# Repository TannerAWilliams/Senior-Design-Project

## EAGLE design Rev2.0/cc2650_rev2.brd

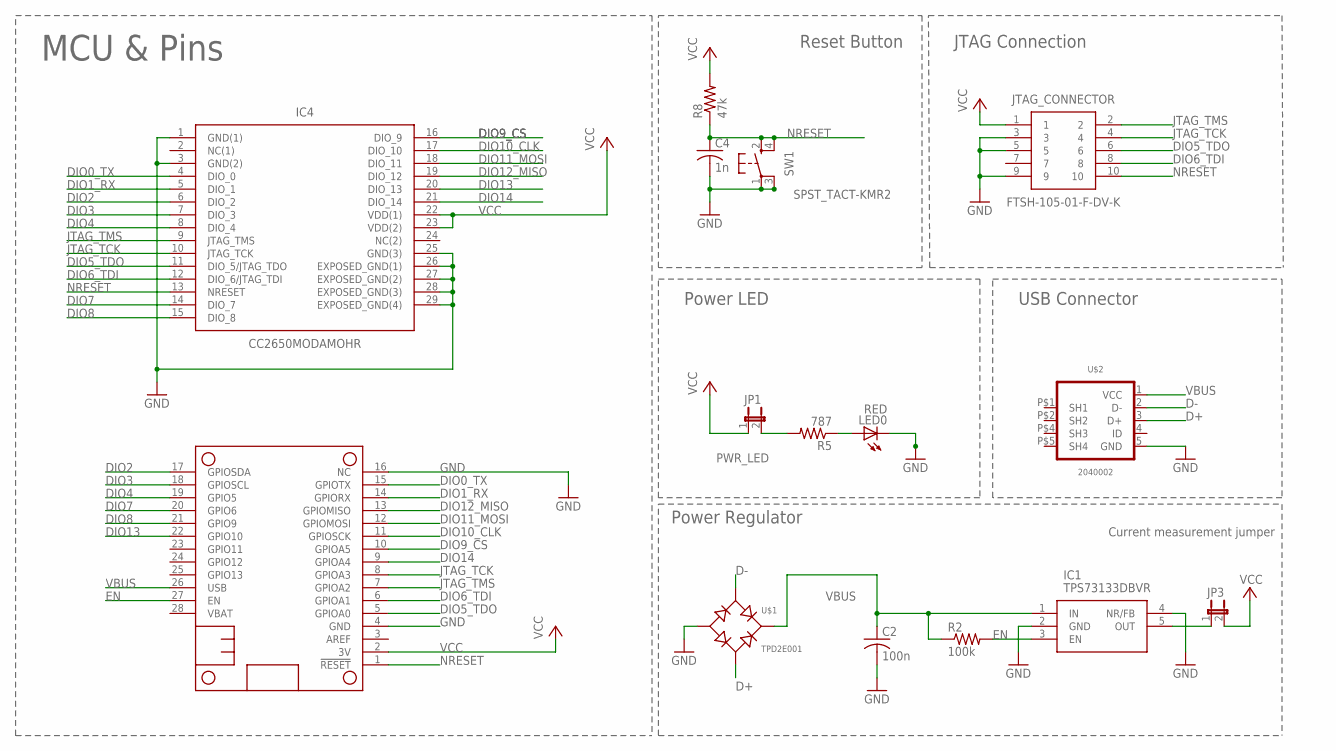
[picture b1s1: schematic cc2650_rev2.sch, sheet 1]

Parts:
C2: 100n; C1206
C4: 1n; C1206
IC1: TPS73133DBVR; SOT95P280X145-5N; MPN TPS73133DBVR
IC4: CC2650MODAMOHR; MOH0029A; MPN CC2650MODAMOHR
JP1, JP3: PWR_LED; JP1M; MPN 2211S-02G
JTAG_CONNECTOR: FTSH-105-01-F-DV-K; SAMTEC_FTSH-105-01-L-DV; MPN FTSH-105-01-F-DV-K
LED0: RED; CHIPLED_0603
MS1: FEATHERWING_NODIM; FEATHERWING_DIM
R2: 100k; R1206
R5: 787; R0603; MPN RC0603JR-07100KL
R8: 47k; R1206
SW1: SPST_TACT-KMR2; KMR2; MPN KMR241G LFS
U$1: TPD2E001; SOT-143
U$2: 2040002

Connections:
D+: U$1.3 (AC2), U$2.3 (D+)
D-: U$1.2 (AC1), U$2.2 (D-)
DIO0_TX: IC4.4 (DIO_0), MS1.15 (GPIOTX)
DIO1_RX: IC4.5 (DIO_1), MS1.14 (GPIORX)
DIO2: IC4.6 (DIO_2), MS1.17 (GPIOSDA); also elsewhere on the board
DIO3: IC4.7 (DIO_3), MS1.18 (GPIOSCL); also elsewhere on the board
DIO4: IC4.8 (DIO_4), MS1.19 (GPIO5)
DIO5_TDO: IC4.11 (DIO_5/JTAG_TDO), JTAG_CONNECTOR.6, MS1.5 (GPIOA0)
DIO6_TDI: IC4.12 (DIO_6/JTAG_TDI), JTAG_CONNECTOR.8, MS1.6 (GPIOA1)
DIO7: IC4.14 (DIO_7), MS1.20 (GPIO6)
DIO8: IC4.15 (DIO_8), MS1.21 (GPIO9)
DIO9_CS: IC4.16 (DIO_9), MS1.10 (GPIOA5)
DIO10_CLK: IC4.17 (DIO_10), MS1.11 (GPIOSCK)
DIO11_MOSI: IC4.18 (DIO_11), MS1.12 (GPIOMOSI)
DIO12_MISO: IC4.19 (DIO_12), MS1.13 (GPIOMISO)
DIO13: IC4.20 (DIO_13), MS1.22 (GPIO10); also elsewhere on the board
DIO14: IC4.21 (DIO_14), MS1.9 (GPIOA4); also elsewhere on the board
EN: IC1.3 (EN), MS1.27 (EN), R2.2
GND: C2.2, C4.2, IC1.2 (GND), IC1.4 (NR/FB), IC4.1 (GND(1)), IC4.3 (GND(2)), IC4.25 (GND(3)), IC4.26 (EXPOSED_GND(1)), IC4.27 (EXPOSED_GND(2)), IC4.28 (EXPOSED_GND(3)), IC4.29 (EXPOSED_GND(4)), JTAG_CONNECTOR.3, JTAG_CONNECTOR.5, JTAG_CONNECTOR.9, LED0.C, MS1.4 (GND), MS1.16 (NC), SW1.1, SW1.3 (P1), U$1.1 (-), U$2.5 (GND); also elsewhere on the board
JTAG_TCK: IC4.10 (JTAG_TCK), JTAG_CONNECTOR.4, MS1.8 (GPIOA3)
JTAG_TMS: IC4.9 (JTAG_TMS), JTAG_CONNECTOR.2, MS1.7 (GPIOA2)
NRESET: C4.1, IC4.13 (NRESET), JTAG_CONNECTOR.10, MS1.1 (!RESET), R8.1, SW1.2 (S), SW1.4 (S1)
PWR_LED: LED0.A, R5.1
PWR_LED_JPR: JP1.2, R5.2
VBUS: C2.1, IC1.1 (IN), MS1.26 (USB), R2.1, U$1.4 (+), U$2.1 (VCC)
VCC: IC4.22 (VDD(1)), IC4.23 (VDD(2)), JP1.1, JP3.2, JTAG_CONNECTOR.1, MS1.2 (3V), R8.2; also elsewhere on the board
VCC_JPR: IC1.5 (OUT), JP3.1

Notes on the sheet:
Current measurement jumper
JTAG Connection
Reset Button
Power Regulator
Power LED
USB Connector
MCU & Pins

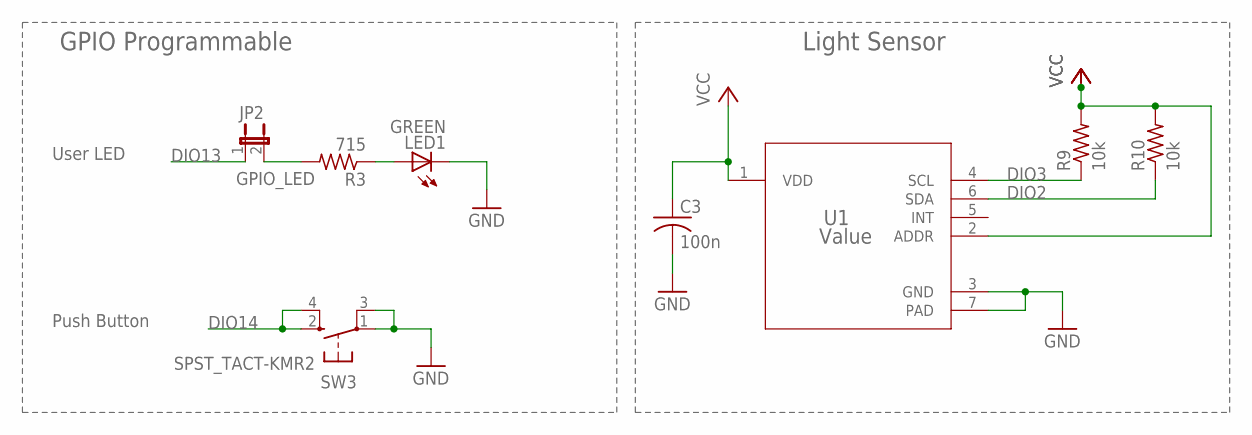
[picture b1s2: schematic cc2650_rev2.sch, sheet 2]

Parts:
C3: 100n; C1206
JP2: GPIO_LED; JP1M; MPN 2211S-02G
LED1: GREEN; CHIPLED_0603
R3: 715; R0603; MPN RC0603JR-07100KL
R9, R10: 10k; R1206
SW3: SPST_TACT-KMR2; KMR2; MPN KMR241G LFS
U1: Value; DNP0006A

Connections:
DIO2: R10.1, U1.6 (SDA); also elsewhere on the board
DIO3: R9.1, U1.4 (SCL); also elsewhere on the board
DIO13: JP2.1; also elsewhere on the board
DIO14: SW3.2 (S), SW3.4 (S1); also elsewhere on the board
GND: C3.2, LED1.C, SW3.1, SW3.3 (P1), U1.3 (GND), U1.7 (PAD); also elsewhere on the board
GPIO_LED: LED1.A, R3.1
GPIO_LED_JPR: JP2.2, R3.2
VCC: C3.1, R9.2, R10.2, U1.1 (VDD), U1.2 (ADDR); also elsewhere on the board

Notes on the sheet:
GPIO Programmable
User LED
Light Sensor
Push Button

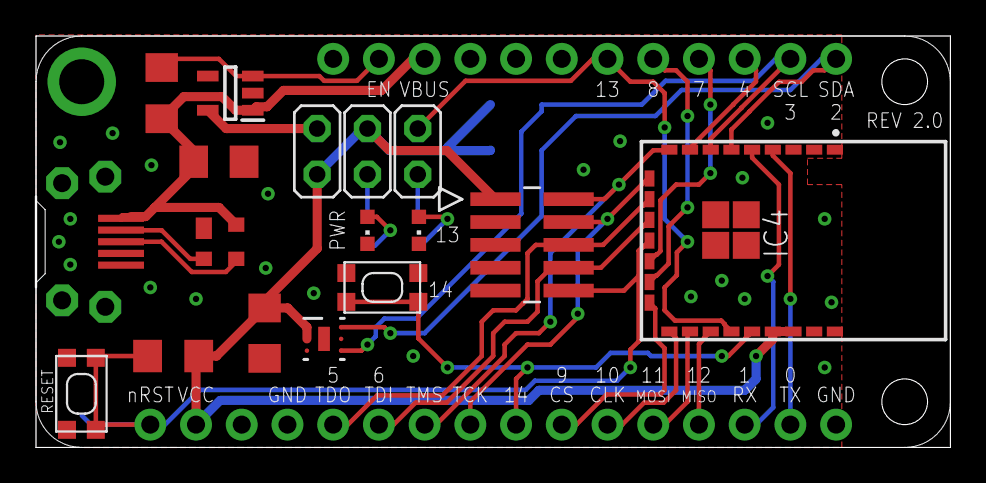
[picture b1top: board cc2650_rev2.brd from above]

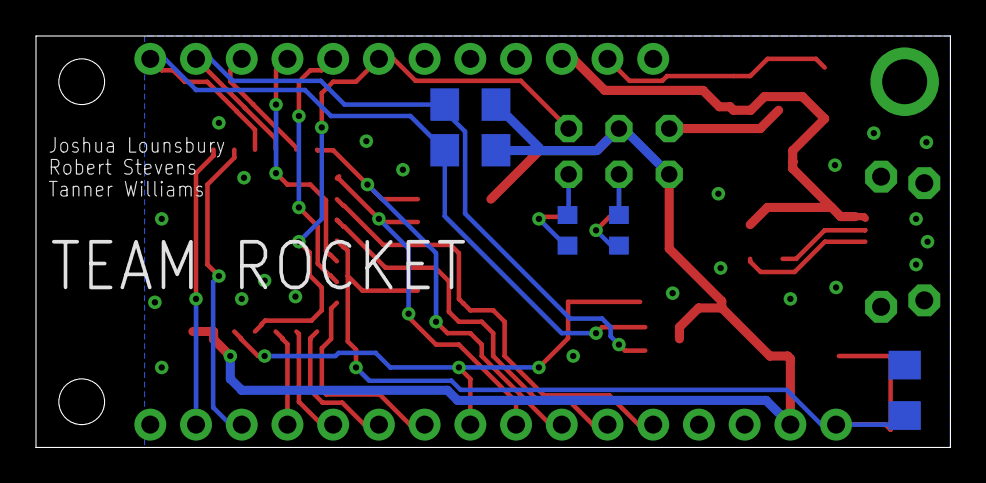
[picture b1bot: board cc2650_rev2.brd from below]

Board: 2 copper layers, 50.8 x 22.9 mm, 23 parts (5 on the bottom side), 29 nets.

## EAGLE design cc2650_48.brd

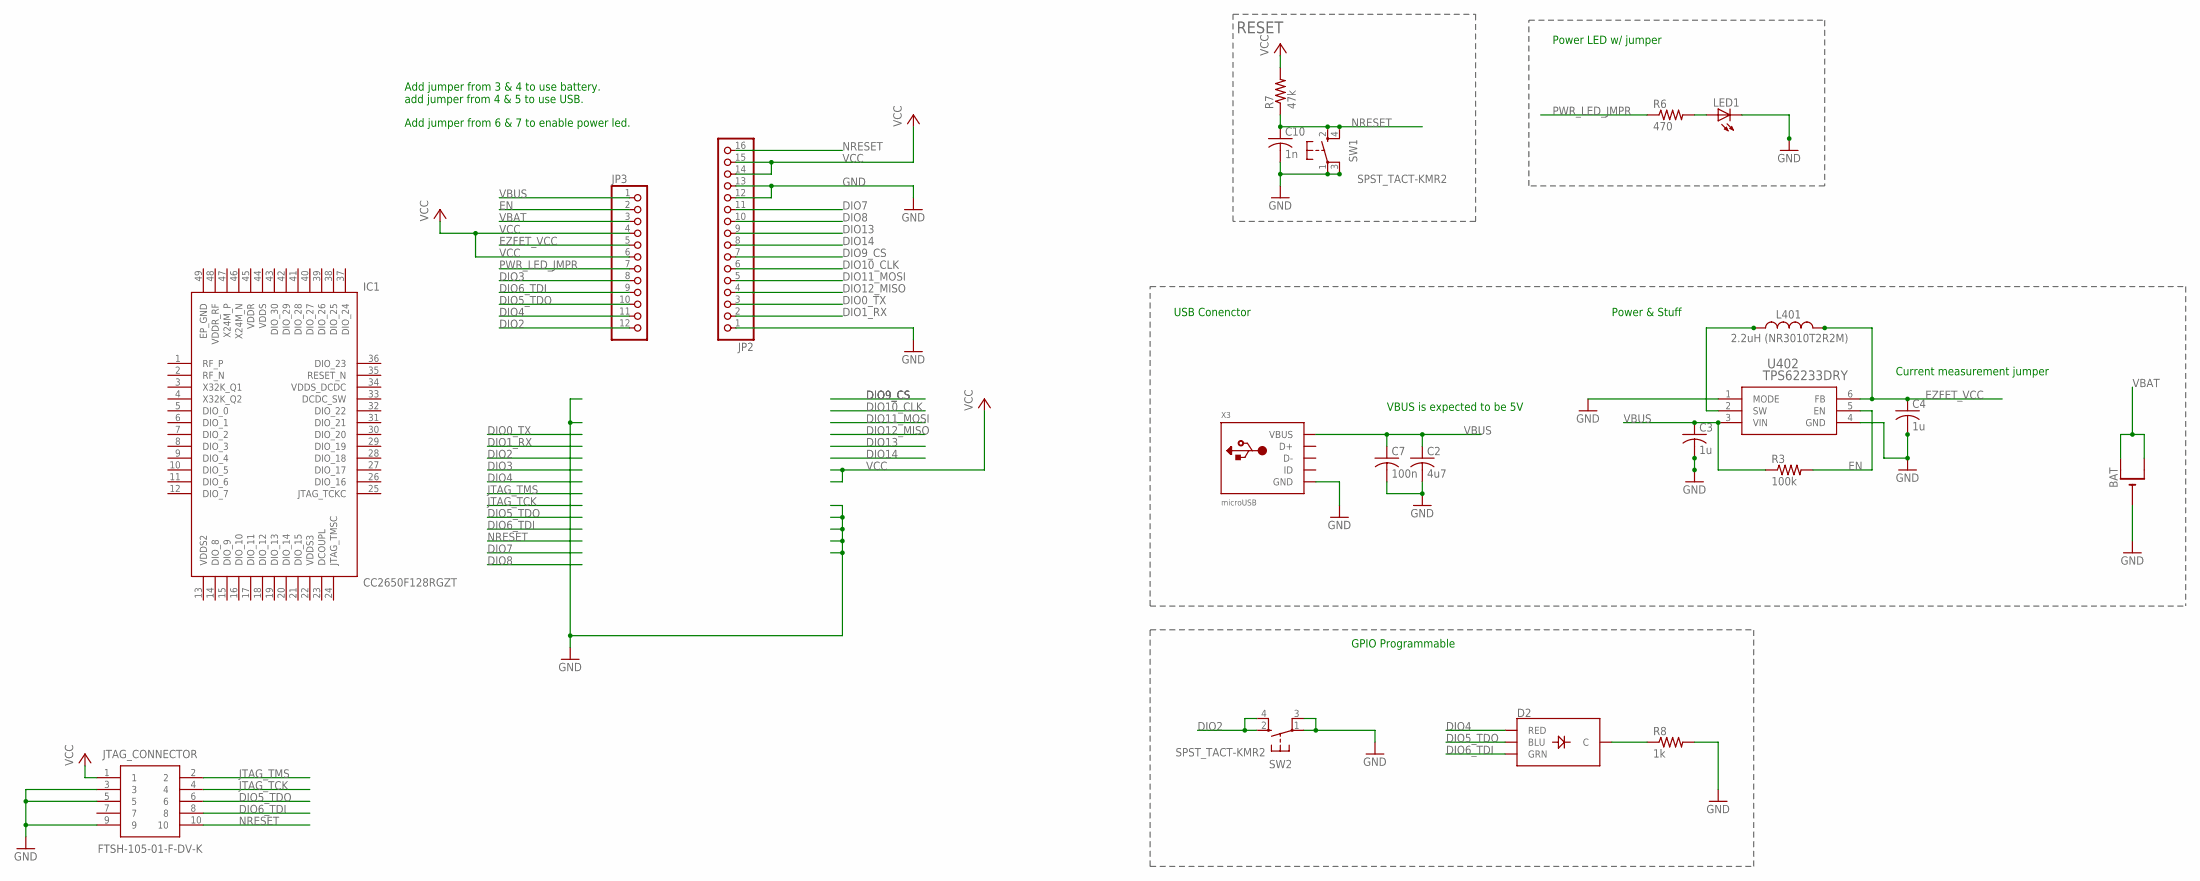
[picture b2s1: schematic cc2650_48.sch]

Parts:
BAT: CR1220THM; CR1220-THM; MPN 3000
C2: 4u7; C1206; MPN GRT31CC81E475KE01L
C3, C4: 1u; C0805; MPN C0805C105K5RACTU
C7: 100n; C0805
C10: 1n; C0805
D2: LED-RGB-CCPIRANHA; LED_PIRANHA_5MM; MPN CLMVB-FKA-CFHEHLCBB7A363
IC1: CC2650F128RGZT; QFN50P700X700X100-49N
JP2: HEADER-1X16ROUND; 1X16_ROUND
JP3: HEADER-1X12; 1X12_ROUND
JTAG_CONNECTOR: FTSH-105-01-F-DV-K; SAMTEC_FTSH-105-01-L-DV; MPN FTSH-105-01-F-DV-K
L401: 2.2uH (NR3010T2R2M); L-NR3010; MPN NR3010T2R2M
LED1: LEDCHIPLED_0805; CHIPLED_0805
R3: 100k; R0805
R6: 470; R0805
R7: 47k; R0805
R8: 1k; R0805
SW1, SW2: SPST_TACT-KMR2; KMR2
U402: TPS62233DRY; DRY6; MPN TPS62233DRYT
X3: microUSB; 4UCONN_20329_V2

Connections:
DIO0_TX: JP2.3
DIO1_RX: JP2.2
DIO2: JP3.12, SW2.2 (S), SW2.4 (S1)
DIO3: JP3.8
DIO4: D2.R (RED), JP3.11
DIO5_TDO: D2.B (BLU), JP3.10, JTAG_CONNECTOR.6
DIO6_TDI: D2.G (GRN), JP3.9, JTAG_CONNECTOR.8
DIO7: JP2.11
DIO8: JP2.10
DIO9_CS: JP2.7
DIO10_CLK: JP2.6
DIO11_MOSI: JP2.5
DIO12_MISO: JP2.4
DIO13: JP2.9
DIO14: JP2.8
EN: JP3.2, R3.2, U402.5 (EN)
EP_GND: IC1.49 (EP_GND)
EZFET_VCC: C4.1, JP3.5, L401.P$2 (2), U402.6 (FB)
GND: BAT.-, C2.2, C3.2, C4.2, C7.2, C10.2, JP2.1, JP2.12, JP2.13, JTAG_CONNECTOR.3, JTAG_CONNECTOR.5, JTAG_CONNECTOR.9, LED1.C, R8.2, SW1.1, SW1.3 (P1), SW2.1, SW2.3 (P1), U402.1 (MODE), U402.4 (GND), X3.BASE@1 (GND), X3.BASE@2 (GND), X3.GND, X3.SPRT@1 (GND), X3.SPRT@2 (GND), X3.SPRT@3 (GND), X3.SPRT@4 (GND)
JTAG_TCK: JTAG_CONNECTOR.4
JTAG_TMS: JTAG_CONNECTOR.2
unnamed: D2.- (C), R8.1
unnamed: L401.P$1 (1), U402.2 (SW)
unnamed: LED1.A, R6.2
NRESET: C10.1, JP2.16, JTAG_CONNECTOR.10, R7.1, SW1.2 (S), SW1.4 (S1)
PWR_LED_JMPR: JP3.7, R6.1
VBAT: BAT.+1 (+), BAT.+2 (+1), JP3.3
VBUS: C2.1, C3.1, C7.1, JP3.1, R3.1, U402.3 (VIN), X3.VBUS
VCC: JP2.14, JP2.15, JP3.4, JP3.6, JTAG_CONNECTOR.1, R7.2
VDDR: IC1.45 (VDDR)
VDDR_RF: IC1.48 (VDDR_RF)
VDDS: IC1.44 (VDDS)
VDDS2: IC1.13 (VDDS2)
VDDS3: IC1.22 (VDDS3)
VDDS_DCDC: IC1.34 (VDDS_DCDC)

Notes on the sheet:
USB Conenctor
RESET
Power LED w/ jumper
Power & Stuff
VBUS is expected to be 5V
Current measurement jumper
GPIO Programmable
Add jumper from 3 & 4 to use battery. add jumper from 4 & 5 to use USB.
Add jumper from 6 & 7 to enable power led.

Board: 2 copper layers, 21 parts (2 on the bottom side), 15 nets, no tracks yet.

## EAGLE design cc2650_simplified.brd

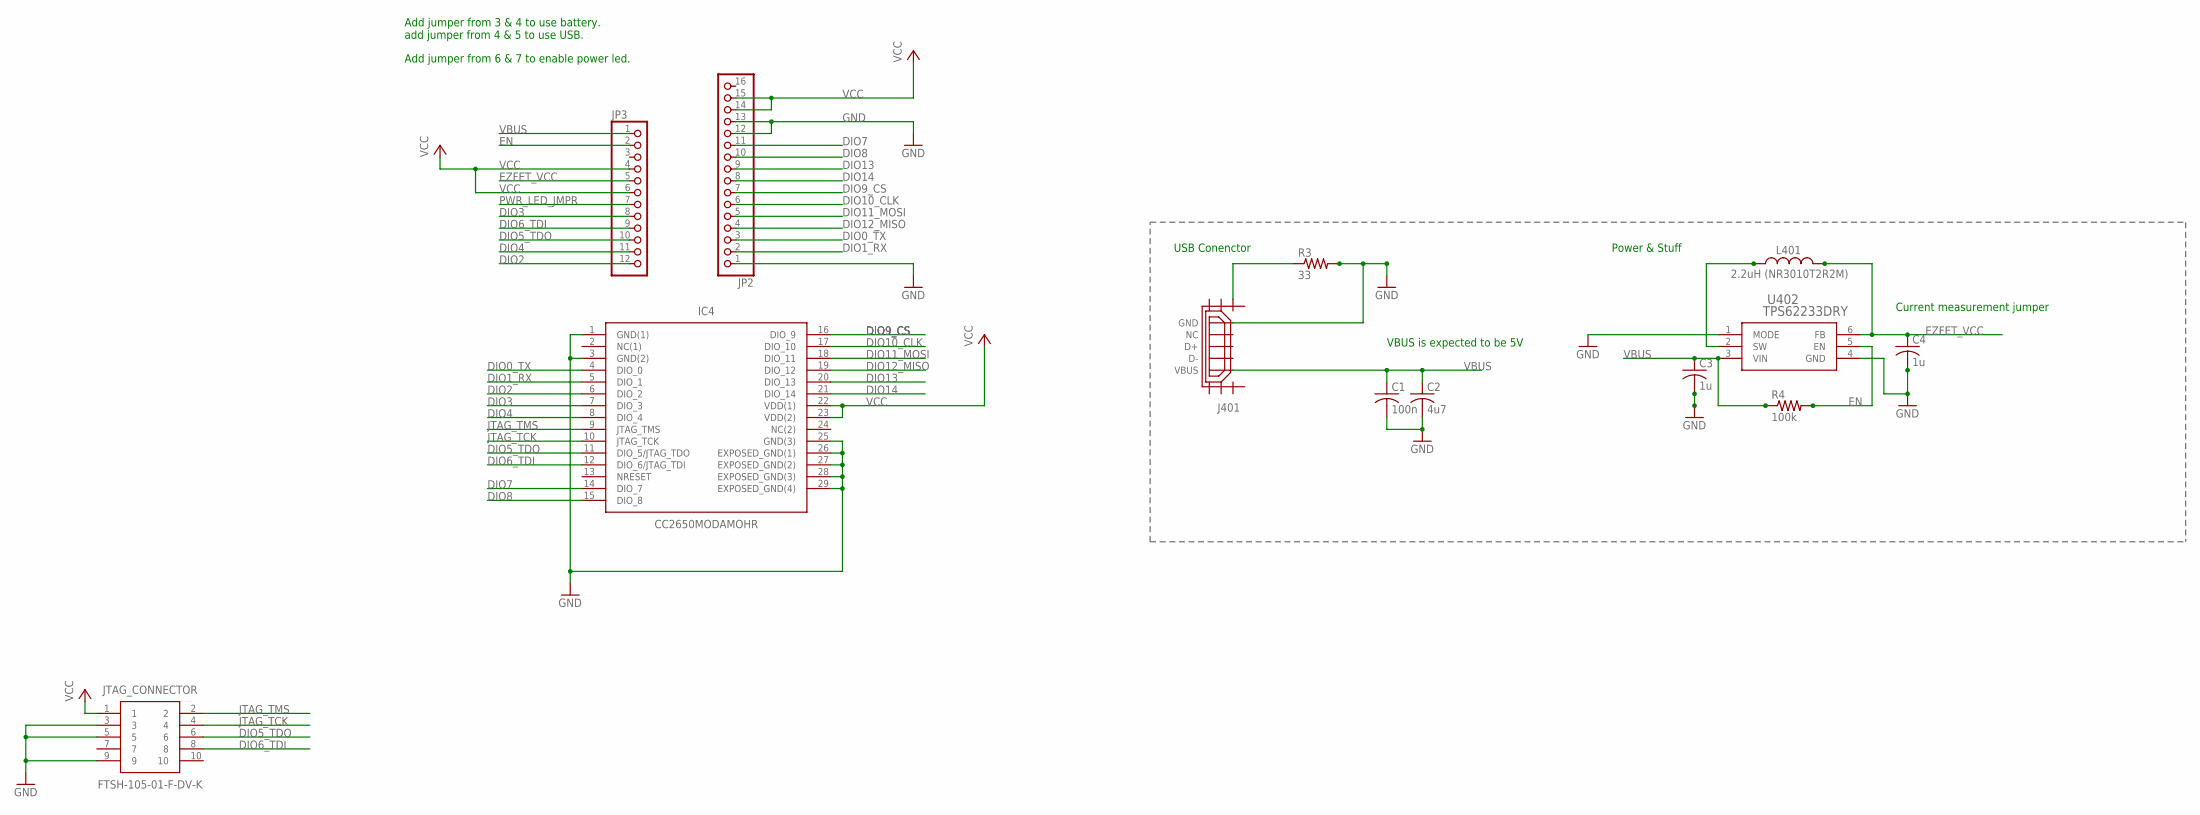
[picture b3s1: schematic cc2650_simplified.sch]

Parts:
C1: 100n; C0402; MPN C1005X7R1H104K050BB
C2: 4u7; C1206; MPN GRT31CC81E475KE01L
C3, C4: 1u; C0805; MPN C0805C105K5RACTU
IC4: CC2650MODAMOHR; MOH0029A; MPN CC2650MODAMOHR
J401: USB_MICRO_FLIPPED; HIROSE-ZX62R-B-5P; MPN ZX62R-B-5P(30)
JP2: HEADER-1X16ROUND; 1X16_ROUND
JP3: HEADER-1X12; 1X12_ROUND
JTAG_CONNECTOR: FTSH-105-01-F-DV-K; SAMTEC_FTSH-105-01-L-DV; MPN FTSH-105-01-F-DV-K
L401: 2.2uH (NR3010T2R2M); L-NR3010; MPN NR3010T2R2M
R3: 33; R0402; MPN ERJ-U02F33R0X
R4: 100k; R0603; MPN RC0603JR-07100KL
U402: TPS62233DRY; DRY6; MPN TPS62233DRYT

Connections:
DIO0_TX: IC4.4 (DIO_0), JP2.3
DIO1_RX: IC4.5 (DIO_1), JP2.2
DIO2: IC4.6 (DIO_2), JP3.12
DIO3: IC4.7 (DIO_3), JP3.8
DIO4: IC4.8 (DIO_4), JP3.11
DIO5_TDO: IC4.11 (DIO_5/JTAG_TDO), JP3.10, JTAG_CONNECTOR.6
DIO6_TDI: IC4.12 (DIO_6/JTAG_TDI), JP3.9, JTAG_CONNECTOR.8
DIO7: IC4.14 (DIO_7), JP2.11
DIO8: IC4.15 (DIO_8), JP2.10
DIO9_CS: IC4.16 (DIO_9), JP2.7
DIO10_CLK: IC4.17 (DIO_10), JP2.6
DIO11_MOSI: IC4.18 (DIO_11), JP2.5
DIO12_MISO: IC4.19 (DIO_12), JP2.4
DIO13: IC4.20 (DIO_13), JP2.9
DIO14: IC4.21 (DIO_14), JP2.8
EN: JP3.2, R4.2, U402.5 (EN)
EZFET_VCC: C4.1, JP3.5, L401.P$2 (2), U402.6 (FB)
GND: C1.2, C2.2, C3.2, C4.2, IC4.1 (GND(1)), IC4.3 (GND(2)), IC4.25 (GND(3)), IC4.26 (EXPOSED_GND(1)), IC4.27 (EXPOSED_GND(2)), IC4.28 (EXPOSED_GND(3)), IC4.29 (EXPOSED_GND(4)), J401.GND, JP2.1, JP2.12, JP2.13, JTAG_CONNECTOR.3, JTAG_CONNECTOR.5, JTAG_CONNECTOR.9, R3.2, U402.1 (MODE), U402.4 (GND)
JTAG_TCK: IC4.10 (JTAG_TCK), JTAG_CONNECTOR.4
JTAG_TMS: IC4.9 (JTAG_TMS), JTAG_CONNECTOR.2
unnamed: J401.SHIELD1, R3.1
unnamed: L401.P$1 (1), U402.2 (SW)
PWR_LED_JMPR: JP3.7
VBUS: C1.1, C2.1, C3.1, J401.VBUS, JP3.1, R4.1, U402.3 (VIN)
VCC: IC4.22 (VDD(1)), IC4.23 (VDD(2)), JP2.14, JP2.15, JP3.4, JP3.6, JTAG_CONNECTOR.1

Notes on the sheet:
USB Conenctor
Power & Stuff
VBUS is expected to be 5V
Current measurement jumper
Add jumper from 3 & 4 to use battery. add jumper from 4 & 5 to use USB.
Add jumper from 6 & 7 to enable power led.

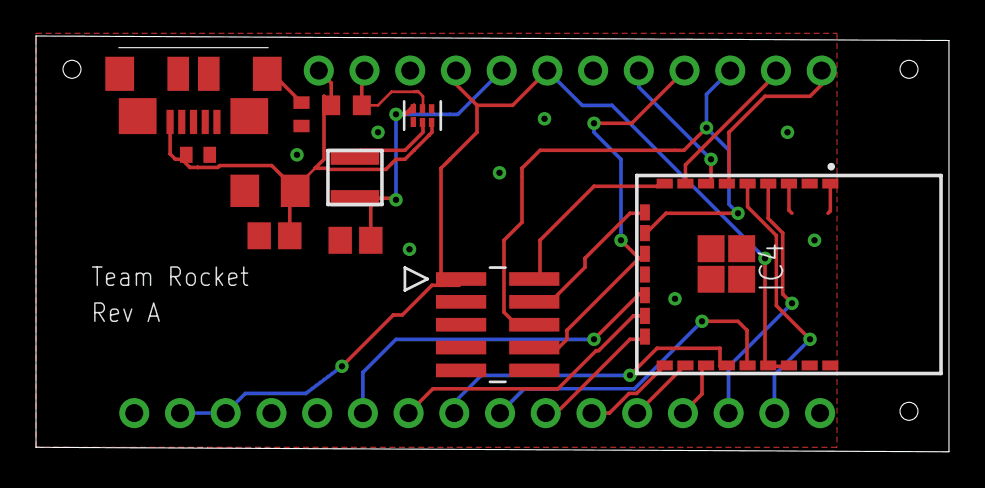
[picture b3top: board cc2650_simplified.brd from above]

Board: 2 copper layers, 50.7 x 23.1 mm, 13 parts (1 on the bottom side), 24 nets.

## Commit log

2017-10-06 MCU Datasheet
2017-10-20 Changed the datasheet to the modular cc2650
2017-10-20 This was the wrong datasheet.
2017-10-20 Remove wrong datasheet.
2017-10-24 Adding Eagle Schematic and Board File
2017-10-25 LED, pushbutton, battery ideas
2017-10-29 made connections to 20 pin headers. added USB power connector.
2017-10-30 added schematic provided by TI.
2017-10-30 reduced board size to match the feather and rearranged some components. Further space optimization is still needed.
2017-11-02 Copied some parts from the LaunchPad example for posible replacement
2017-11-02 Remove one of the 20 pin headers. Added some power components and connections.
2017-11-03 added physical board assembly pdf.
2017-11-03 Changed a few connections and rearranged board layout.
2017-11-03 Uploaded initial schematic and board layouts as pictures.
2017-11-03 created initial schematic and board layouts. Some additional connections required. use command 'RIPUP;' in board layout to erase ALL signal generated by autorouter.
2017-11-03 Changed RGB LED.
2017-11-10 changed pinout.
2017-11-10 changed pinout and added second routing path.
2017-11-10 changed usb connector
2017-11-10 Changed USB connector. Fixed error.
2017-11-10 removed jumpers for power and leds.
2017-11-10 changed out battery to cc1220.
2017-11-10 added routes
2017-11-10 added routes. removed signal by antenna.
2017-11-12 Added GND planes. Replaced some schematic symbols w/ US ones.
2017-11-12 changed some pins. added bom through eagle.
2017-11-12 added bom though eagle. added gnd planes. replaced some symbols.
2017-11-12 added bom though eagle. added gnd planes. rearranged board.
2017-11-13 changed 100k resistor to in stock.
2017-11-13 added connections for RGB LED and push button.
2017-11-13 added board routing. 20 vias total.7 connect gnd planes.
2017-11-13 modified board routing. 21 vias total. 8 connect gnd planes.
2017-11-14 fixed gnd connection on USB.
2017-11-14 minor routing changes.
2017-11-16 Simplified board so far. Need to look at ground issue.
2017-11-16 Changed Voltage Regulator to 3.3V output.
2017-11-17 fixed broken connection and missing via.
2017-11-17 fixed minor connections.
2017-11-17 moved headers & usb away from edge of board
2017-11-17 board size, gerber files
2017-11-17 fixed silkscreen
2017-11-17 added gerber files
2017-11-17 fixed 1 wire and silkscreen
2017-11-26 Added block diagram xml and png files.
2017-12-07 added 48 pin cc2650. change R&C to bigger packages.
2017-12-07 added 48 pin cc2650. change res, cap, led to bigger packages. moved battery to bottom of board. changed micro usb.
2018-01-19 Unwanted files
2018-01-22 Removed battery, ripped up connections to move things around and add sensors. Need to replace usb with through hole connector.
2018-01-29 Added light sensor.
2018-01-31 Switched out USB connector.
2018-01-31 Changed position of holes, fixed dimensions.
2018-01-31 Changred USB connector to TH.
2018-02-02 Added light sensor connections.
2018-02-02 Changed the pins for the light sensor connection.
2018-02-07 added dimension on layer 47 (measure)
2018-02-07 added new power regulator to schematic.
2018-02-07 added coin cell from adafruit. added holes and RGB LED from MSP432.
2018-02-07 re-arranged schematic.
2018-02-08 changed R & C size to 1206. may need to consider 0805.
2018-02-08 changed top gnd plane under cc2650 under RF test pads.
2018-02-08 changed headers arrangement.
2018-02-08 rearranged some components.
2018-02-09 Moved around some parts.
2018-02-14 Got rid of text.
2018-02-14 moved some components to bottom side of the board.
2018-02-14 changed btn pin from DIO4 -> DIO14. Rotated/moved res.
2018-02-15 completed BOM through eagle. RGB led not in eagle choices. 12 & 16 pin headers chosen as signle adafruit feather pin kit.
2018-02-16 added 100k res between EN and VBUS and added EN to pin headers. Changed coin cell holder to external connector.
2018-02-16 switched usb and battery connection to match real feather layout. moved some other components to compensate.
2018-02-20 modified adafruit FeatehrWing pin part to remove bottom left hole. Swapped modified FeatherWing for the 1x12 & 1x16 pin headers.
2018-02-22 removed RGB LED. Removed extra power pins from pin headers.
2018-02-22 changed resistor values for LEDS.
2018-02-23 changed power circuitry
2018-02-23 Changed power circuitry. Added TI ESD Suppresor.
2018-02-25 changed usb to AMP lab part.
2018-02-25 changed USB circuit to closer match layout of AMP card.
2018-02-25 rearranged some components and hand routed some power signals.
2018-02-26 routed everything but light sensor
2018-02-26 added one missed VCC connection
2018-02-26 fixed a few missing connections.
2018-02-26 fixed a few missing connection to gnd on resistor in bottomw left.
2018-02-26 fixed a connection on D-.
2018-02-26 changed minor things based of feedback from Dz-Da Sung.
2018-02-27 hand routed wires at 10 MIL and power at 20 MIL. still one issue in DRC with VBUS wire on USB. Cleaned up schematic to make things more compact.
2018-02-27 fixed issue with VBUS on usb in DRC.
2018-02-27 added some silk screen
2018-02-27 added silkscreen to all pins.
2018-02-27 changed silkscreen text size to .24
2018-02-27 added more vias to gnd planes and REV 1.0
2018-02-27 added a few more vias
2018-03-20 added archive of rev1
2018-03-20 removed gnd plane vias.
2018-03-20 rearranged gpio LEDs and button. moved JATG connector to center of board.
2018-03-20 moved some silkscreen. made size consistant.
2018-03-20 changed silkscreen around LED/button. Added names to back side of board.
2018-03-20 moved gpio button down from LEDs. reduced 'Team Rocket' font size on back so it doesn't interfere with resistors on back.
2018-03-20 added extra gnd plane vias
2018-03-20 removed one silkscreen object on backside.
2018-03-20 added archive of rev 1.1.
2018-03-23 added light sensor to schematic, but not placed on board. Cleaned up text on schematic.
2018-03-23 moved light sensor to board and added VCC connections.
2018-03-23 Removed text from light sensor and changed sensor position.
2018-03-23 changed resistors and LEDs to 0603, capacitors to 0805.
2018-03-23 tweaked some component positions.
2018-03-26 completed light sensor wire routing. TODO: clean up silk screen, increase R/C size to 1206 to use old parts.
2018-03-26 changed component size to 1206 except LED circuits.
2018-03-26 fixed missing connection on button.
2018-03-26 cleaned up silkscreen. changed light sensor cap to 1206.
2018-03-26 added extra vias to gnd planes
2018-03-26 moved LED and button 13 & 14 silk screen. Changed DIO5, 6 silkcreen with TDI/TDO. Reduced 'TEAM ROCKET' text size.
2018-03-26 reduced 'TEAM ROCKET' silkscreen size.
2018-03-26 changed names silkscreen
2018-03-26 added gerber files for rev 2.0
2018-03-26 added archive copy of rev 2.0
2018-03-26 added pdf schematics
2018-03-29 fixed drill .txt file. added t\bvalues to silkscreen layers in CAM processor.
2018-04-04 software example that toggles LED with button press for board REV 1.0. Uses TI-RTOS.
2018-04-23 Added Rev 2.1 by removing GND signal on power regulator that was causing an issue.
2018-04-23 Added Rev 1.2 by removing GND signal on power regulator that was causing an issue.
2018-04-23 reuploaded schematic pdf with out time caption on bottom.
2018-04-23 added individual folders for each revision.
2018-04-23 moved booster pack datasheet, schematic, and assembly pdf to sperate folder.
2018-04-23 moved old design files to new folder.
2018-04-23 removed file that was copied to folder
2018-04-23 removed files that were copied to seperate folders.
2018-04-23 removed files that were copied into seperate folders.
2018-04-23 removed block diagrams folder an put in old design files folder
2018-04-27 added software example .zip files
2018-05-08 added User's Guide

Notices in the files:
parts and their libraries:
SparkFun-LED: Licensing: Creative Commons ShareAlike 4.0 International - https://creativecommons.org/licenses/by-sa/4.0
microbuilder: This work is placed in the public domain, and may be freely used for commercial and non-commercial work with the following conditions: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
